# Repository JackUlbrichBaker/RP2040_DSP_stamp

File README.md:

# Scraped as the RP2350 has been released

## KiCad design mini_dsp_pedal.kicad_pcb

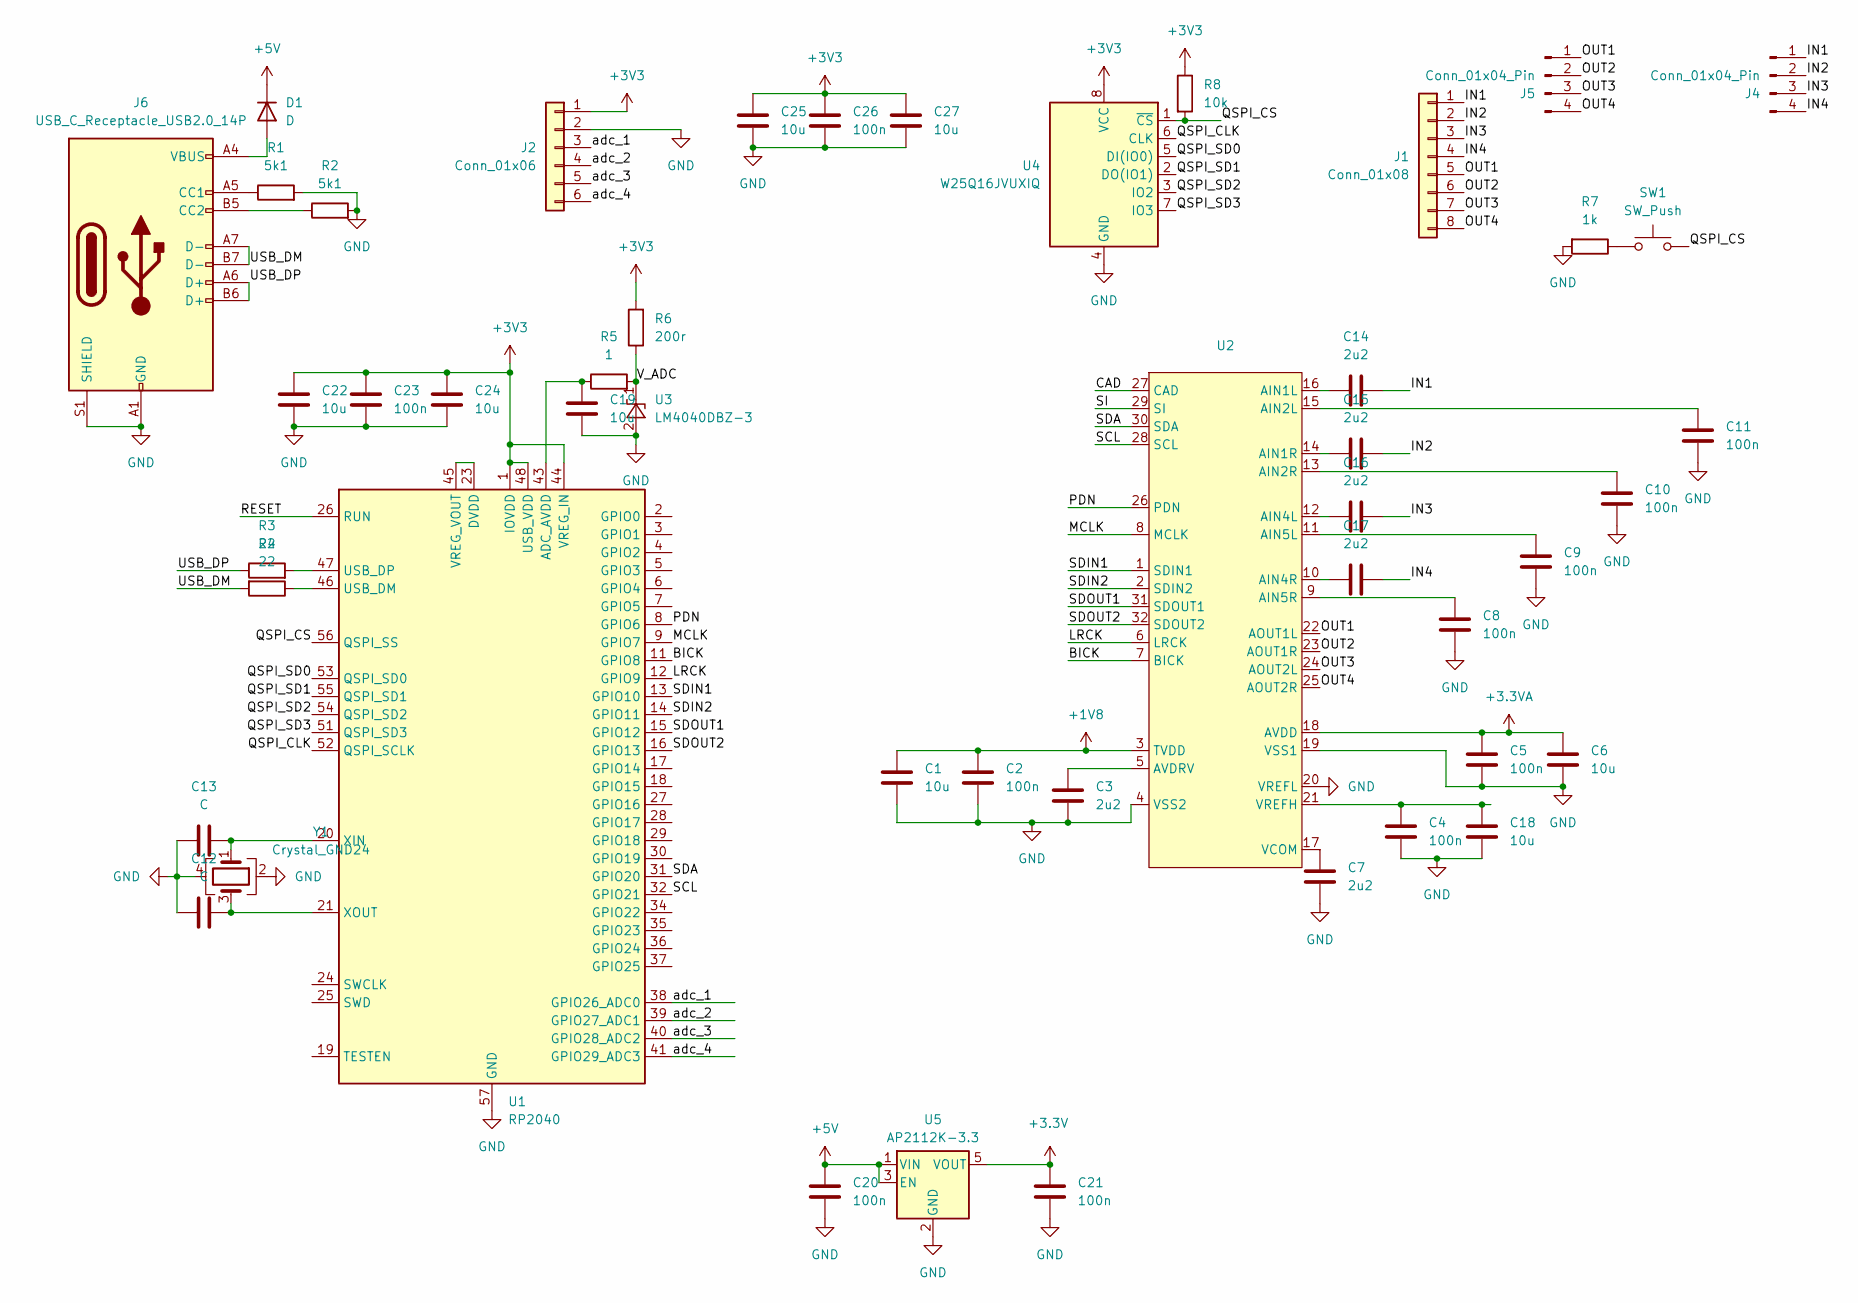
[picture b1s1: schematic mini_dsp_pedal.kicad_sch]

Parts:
C1, C6, C18, C19, C22, C24, C25, C27: 10u; C_0603_1608Metric
C2, C4, C5, C8, C9, C10, C11, C20, C21, C23, C26: 100n; C_0603_1608Metric
C3, C7, C14, C15, C16, C17: 2u2; C_0603_1608Metric
C12, C13: C; C_0603_1608Metric
D1: D; D_0603_1608Metric
J1: Conn_01x08; PinHeader_1x08_P2.54mm_Vertical_SMD_Pin1Right
J2: Conn_01x06; PinHeader_1x06_P2.54mm_Vertical_SMD_Pin1Right
J4, J5: Conn_01x04_Pin; PinHeader_1x04_P2.54mm_Vertical_SMD_Pin1Left
J6: USB_C_Receptacle_USB2.0_14P; USB_C_Receptacle_GCT_USB4105-xx-A_16P_TopMnt_Horizontal
R1, R2: 5k1; R_0603_1608Metric
R3, R4: 22; R_0603_1608Metric
R5: 1; R_0603_1608Metric
R6: 200r; R_0603_1608Metric
R7: 1k; R_0603_1608Metric
R8: 10k; R_0603_1608Metric
SW1: SW_Push; SW_Push_1P1T_XKB_TS-1187A
U1: RP2040; QFN-56-1EP_7x7mm_P0.4mm_EP3.2x3.2mm
U2: QFN-32-1EP_5x5mm_P0.5mm_EP3.7x3.7mm_ThermalVias
U3: LM4040DBZ-3; SOT-23
U4: W25Q16JVUXIQ; SOIC-8_5.23x5.23mm_P1.27mm
U5: AP2112K-3.3; SOT-23-5
Y1: Crystal_GND24; Crystal_SMD_Abracon_ABM3C-4Pin_5.0x3.2mm

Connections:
+1V8: C1.1, C2.1, U2.3 (TVDD)
+3.3V: C21.1, U5.5 (VOUT)
+3.3VA: C5.1, C6.1, U2.18 (AVDD)
+3V3: C22.1, C23.1, C24.1, C25.1, C26.1, C27.1, J2.1, R6.2, R8.1, U1.1 (IOVDD), U1.10 (IOVDD), U1.22 (IOVDD), U1.33 (IOVDD), U1.42 (IOVDD), U1.44 (VREG_IN), U1.48 (USB_VDD), U1.49 (IOVDD), U4.8 (VCC)
+5V: C20.1, D1.1 (K), U5.1 (VIN), U5.3 (EN)
/BICK: U1.11 (GPIO8), U2.7 (BICK)
/CAD: U2.27 (CAD)
/IN1: C14.2, J1.1, J4.1
/IN2: C15.2, J1.2, J4.2
/IN3: C16.2, J1.3, J4.3
/IN4: C17.2, J1.4, J4.4
/LRCK: U1.12 (GPIO9), U2.6 (LRCK)
/MCLK: U1.9 (GPIO7), U2.8 (MCLK)
/OUT1: J1.5, J5.1, U2.22 (AOUT1L)
/OUT2: J1.6, J5.2, U2.23 (AOUT1R)
/OUT3: J1.7, J5.3, U2.24 (AOUT2L)
/OUT4: J1.8, J5.4, U2.25 (AOUT2R)
/PDN: U1.8 (GPIO6), U2.26 (PDN)
/QSPI_CLK: U1.52 (QSPI_SCLK), U4.6 (CLK)
/QSPI_CS: R8.2, SW1.2, U1.56 (QSPI_SS), U4.1 (~CS)
/QSPI_SD0: U1.53 (QSPI_SD0), U4.5 (DI(IO0))
/QSPI_SD1: U1.55 (QSPI_SD1), U4.2 (DO(IO1))
/QSPI_SD2: U1.54 (QSPI_SD2), U4.3 (IO2)
/QSPI_SD3: U1.51 (QSPI_SD3), U4.7 (IO3)
/RESET: U1.26 (RUN)
/SCL: U1.32 (GPIO21), U2.28 (SCL)
/SDA: U1.31 (GPIO20), U2.30 (SDA)
/SDIN1: U1.13 (GPIO10), U2.1 (SDIN1)
/SDIN2: U1.14 (GPIO11), U2.2 (SDIN2)
/SDOUT1: U1.15 (GPIO12), U2.31 (SDOUT1)
/SDOUT2: U1.16 (GPIO13), U2.32 (SDOUT2)
/SI: U2.29 (SI)
/USB_DM: J6.A7 (D-), J6.B7 (D-), R4.2
/USB_DP: J6.A6 (D+), J6.B6 (D+), R3.1
/V_ADC: R5.2, R6.1, U3.1 (K)
/adc_1: J2.3, U1.38 (GPIO26_ADC0)
/adc_2: J2.4, U1.39 (GPIO27_ADC1)
/adc_3: J2.5, U1.40 (GPIO28_ADC2)
/adc_4: J2.6, U1.41 (GPIO29_ADC3)
GND: C1.2, C2.2, C3.2, C4.2, C5.2, C6.2, C7.2, C8.2, C9.2, C10.2, C11.2, C12.1, C13.1, C18.2, C19.2, C20.2, C21.2, C22.2, C23.2, C24.2, C25.2, C26.2, C27.2, J2.2, J6.A1 (GND), J6.A12 (GND), J6.B1 (GND), J6.B12 (GND), J6.S1 (SHIELD), R1.2, R2.2, R7.2, U1.57 (GND), U2.4 (VSS2), U2.19 (VSS1), U2.20 (VREFL), U3.2 (A), U4.4 (GND), U5.2 (GND), Y1.2, Y1.4
unnamed: D1.2 (A), J6.A4 (VBUS), J6.A9 (VBUS), J6.B4 (VBUS), J6.B9 (VBUS)
unnamed: J6.A5 (CC1), R1.1
unnamed: J6.B5 (CC2), R2.1
unnamed: R7.1, SW1.1
unnamed: C19.1, R5.1, U1.43 (ADC_AVDD)
unnamed: R4.1, U1.46 (USB_DM)
unnamed: R3.2, U1.47 (USB_DP)
unnamed: U1.23 (DVDD), U1.45 (VREG_VOUT), U1.50 (DVDD)
unnamed: C13.2, U1.20 (XIN), Y1.1
unnamed: C12.2, U1.21 (XOUT), Y1.3
unnamed: C14.1, U2.16 (AIN1L)
unnamed: C15.1, U2.14 (AIN1R)
unnamed: C11.1, U2.15 (AIN2L)
unnamed: C10.1, U2.13 (AIN2R)
unnamed: C16.1, U2.12 (AIN4L)
unnamed: C17.1, U2.10 (AIN4R)
unnamed: C9.1, U2.11 (AIN5L)
unnamed: C8.1, U2.9 (AIN5R)
unnamed: C3.1, U2.5 (AVDRV)
unnamed: C7.1, U2.17 (VCOM)
unnamed: C4.1, C18.1, U2.21 (VREFH)

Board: 2 copper layers, 46 parts (2 on the bottom side), 58 nets, no tracks yet.
